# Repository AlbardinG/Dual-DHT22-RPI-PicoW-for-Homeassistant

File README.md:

# Dual-DHT22-RPI-for-Homeassistant

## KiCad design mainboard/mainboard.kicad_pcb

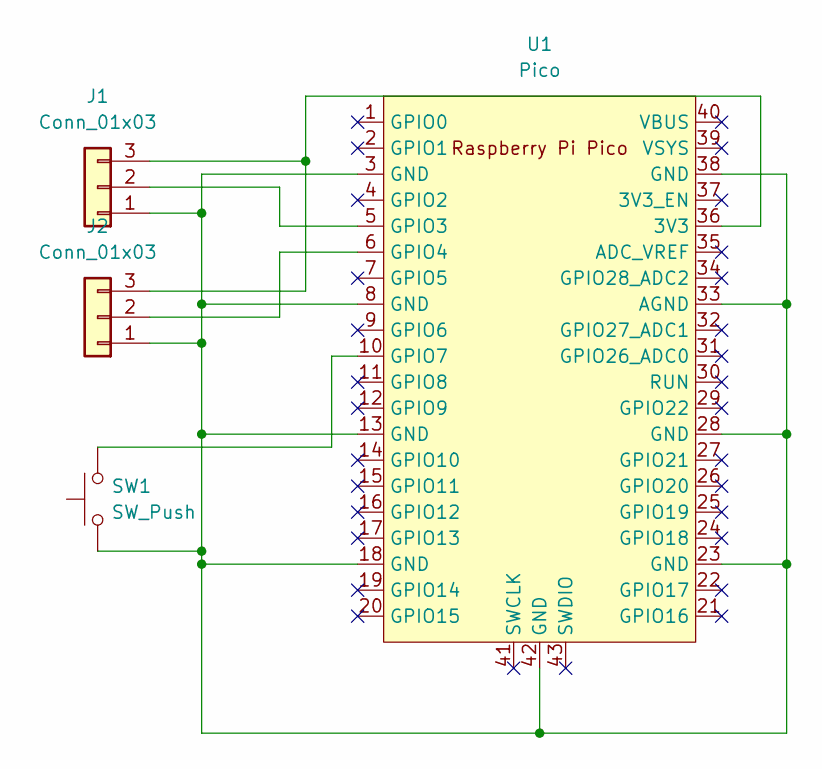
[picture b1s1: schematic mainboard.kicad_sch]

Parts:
J1, J2: Conn_01x03; JST_EH_B3B-EH-A_1x03_P2.50mm_Vertical
SW1: SW_Push; KSA_Tactile_SPST
U1: Pico; RPi_Pico_SMD_TH

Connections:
unnamed: J1.2, U1.5 (GPIO3)
unnamed: J1.3, J2.3, U1.36 (3V3)
unnamed: J1.1, J2.1, SW1.1, U1.3 (GND), U1.8 (GND), U1.13 (GND), U1.18 (GND), U1.23 (GND), U1.28 (GND), U1.33 (AGND), U1.38 (GND), U1.42 (GND)
unnamed: J2.2, U1.6 (GPIO4)
unnamed: SW1.2, U1.10 (GPIO7)

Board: 2 copper layers, 4 parts (0 on the bottom side), 5 nets, no tracks yet.

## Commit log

2023-03-19 main code
    setup
2023-03-23 update for pcb
2023-03-31 code update
